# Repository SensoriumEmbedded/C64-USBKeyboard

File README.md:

# C64-USBKeyboard

## USB keyboard interface for Commodore 64

**Original code and C64 Key Pos Mapping:**
* C64keyboard - Commodore Keyboard library
* Copyright (c) 2022 Hartland PC LLC, Written by Robert VanHazinga

**Rewritten/updated for Teensy 3.6/4.1:**
* Copyright (c) 2023 Sensorium Embedded, Written by Travis Smith
* Raw keypresss detection for improved emulation
* Ability to Shift special macro keys to c64 (F2/4/6/8, Cursor up/left, etc) 
* Diagnostics loopback emulation
* Symbol mapping for readability and easy editing
* Improved code clarity, fixed bugs
* PCB designed/added

PCB assembly instructions can be found **[here.](PCB/PCB_Assembly.md)**

Questions?  Send e-mail to [Travis @ Sensorium](mailto:travis@sensoriumembedded.com)

Stand-alone and in-system pictures below.  Note that I have sockets above and below the Teensy module in my build. Actual build per BOM using headers will make it sit much lower (similar to the MT8808 chip)
||| 
|:--:|:--:|

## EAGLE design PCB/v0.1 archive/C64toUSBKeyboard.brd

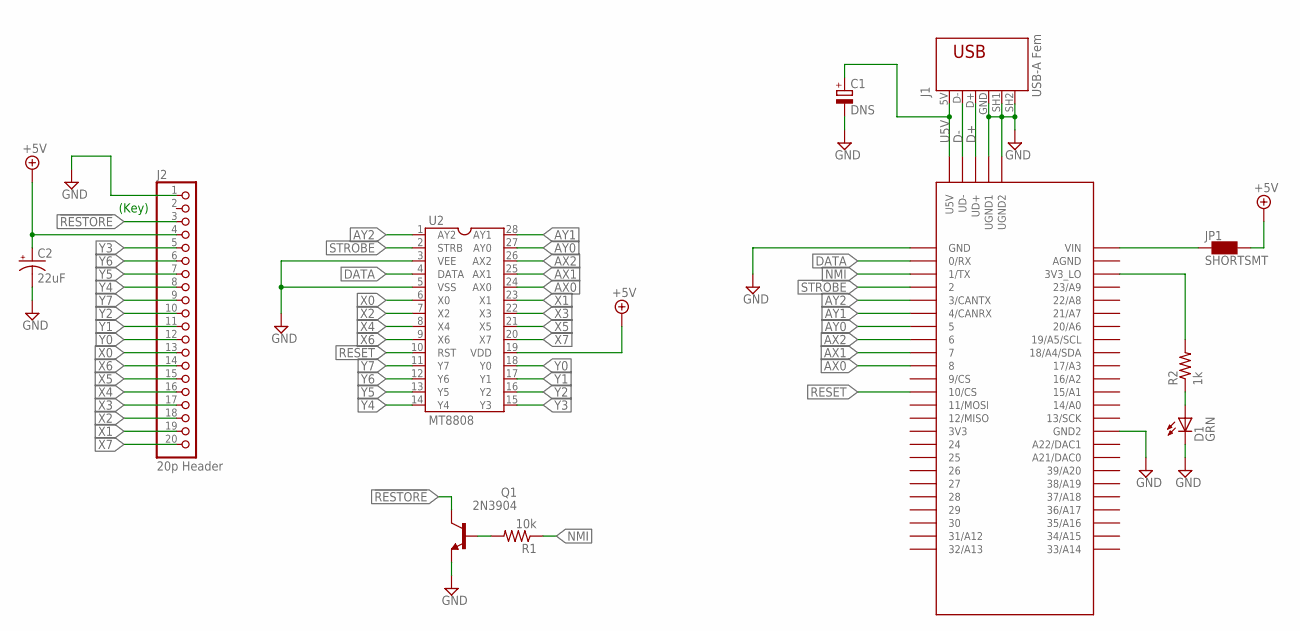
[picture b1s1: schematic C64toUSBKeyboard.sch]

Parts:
C1: DNS; A/3216-18W
C2: 22uF; E2,5-6
D1: GRN; LED-3MM-PTH
J1: USB-A Fem; USB
J2: 20p Header; 1X20_ROUND
JP1: SHORTSMT; SHORT
Q1: 2N3904; TO92
R1: 10k; 0207/10
R2: 1k; 0207/10
U1: TEENSY_3.6_4.1; TEENSY_3.5/3.6
U2: MT8808; DIL28-6

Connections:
3V3: R2.2, U1.3V3_LO
5V_TEENSY: JP1.1, U1.VIN
!RESTORE: J2.3, Q1.1 (C)
+5V: C2.+, J2.4, JP1.2, U2.19 (VDD)
AX0: U1.8, U2.24 (AX0)
AX1: U1.7, U2.25 (AX1)
AX2: U1.6, U2.26 (AX2)
AY0: U1.5, U2.27 (AY0)
AY1: U1.4/CANRX, U2.28 (AY1)
AY2: U1.3/CANTX, U2.1 (AY2)
D+: J1.D+ (3), U1.UD+
D-: J1.D- (2), U1.UD-
DATA: U1.0/RX, U2.4 (DATA)
GND: C1.-, C2.-, D1.K (C), J1.GND (4), J1.SH1 (5), J1.SH2 (6), J2.1, Q1.3 (E), U1.GND, U1.GND2, U1.UGND1, U1.UGND2, U2.3 (VEE), U2.5 (VSS)
LED_R: D1.A, R2.1
NMI: R1.1, U1.1/TX
NMI_R: Q1.2 (B), R1.2
RESET: U1.10/CS, U2.10 (RST)
STROBE: U1.2, U2.2 (STRB)
U5V: C1.+, J1.5V (1), U1.U5V
X0: J2.13, U2.6 (X0)
X1: J2.19, U2.23 (X1)
X2: J2.18, U2.7 (X2)
X3: J2.17, U2.22 (X3)
X4: J2.16, U2.8 (X4)
X5: J2.15, U2.21 (X5)
X6: J2.14, U2.9 (X6)
X7: J2.20, U2.20 (X7)
Y0: J2.12, U2.18 (Y0)
Y1: J2.11, U2.17 (Y1)
Y2: J2.10, U2.16 (Y2)
Y3: J2.5, U2.15 (Y3)
Y4: J2.8, U2.14 (Y4)
Y5: J2.7, U2.13 (Y5)
Y6: J2.6, U2.12 (Y6)
Y7: J2.9, U2.11 (Y7)

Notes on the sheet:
(Key)

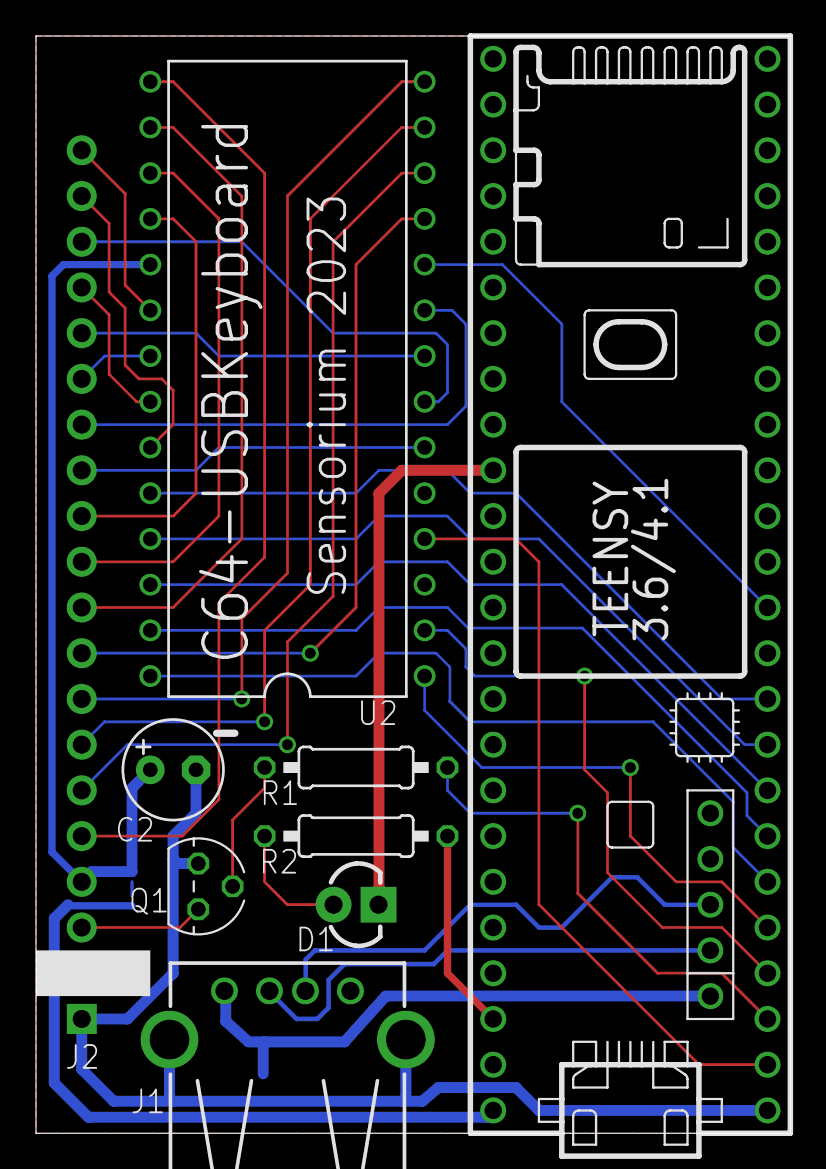
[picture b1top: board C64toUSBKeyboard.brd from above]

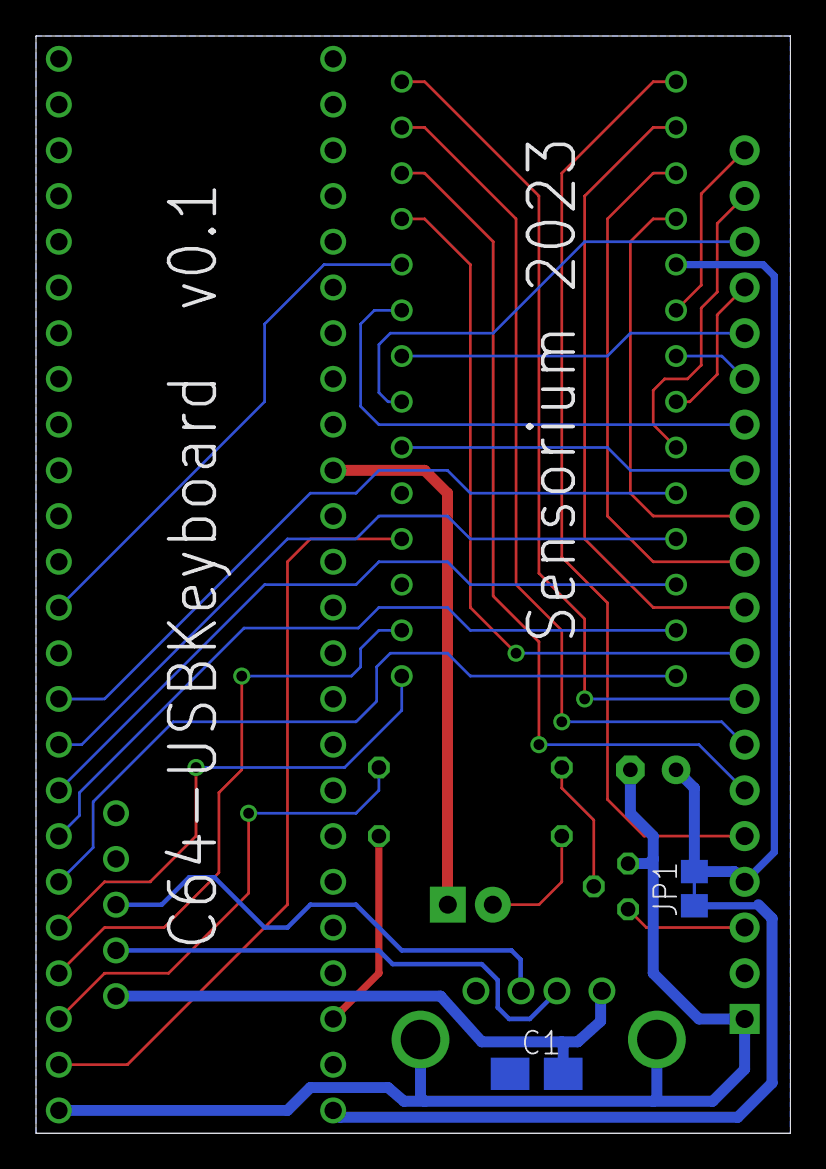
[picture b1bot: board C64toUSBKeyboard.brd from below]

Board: 2 copper layers, 41.9 x 61.0 mm, 11 parts (2 on the bottom side), 36 nets.

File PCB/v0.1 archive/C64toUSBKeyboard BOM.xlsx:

Qty | Value | Device | Package | Parts | Description | DIGIKEY | MANUF1 | MPN1 | VALUE
1 | 10k | R-US_0207/10 | 0207/10 | R1 | RESISTOR, American symbol
1 | 1k | R-US_0207/10 | 0207/10 | R2 | RESISTOR, American symbol
1 | 20p Header | HEADER-1X20ROUND | 1X20_ROUND | J2
1 | 22uF | CPOL-USE2.5-6 | E2,5-6 | C2 | POLARIZED CAPACITOR, American symbol
1 | 2N3904 | 2N3904 | TO92 | Q1 | NPN TRANSISTOR
1 | DNS | CPOL-EUA/3216-18W | A/3216-18W | C1 | POLARIZED CAPACITOR, European symbol
1 | GRN | LED-3MM-GRN | LED-3MM-PTH | D1 | LED 3.1MM PTH | 516-1293-ND | Broadcom Limited | HLMP-1503 | GRN
1 | MT8808 | DIL28 | DIL28-6 | U2 | Dual In Line
1 | SHORTSMT | SHORTSMT | SHORT | JP1
1 | TEENSY_3.6_4.1 | TEENSY_3.5/3.6 | TEENSY_3.5/3.6 | U1
1 | USB-A Fem | USB-787616 | USB | J1 | AMP connector

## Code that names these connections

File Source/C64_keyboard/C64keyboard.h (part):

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
//Teensy Pin Mapping
#define MT8808_DATA_PIN        0 // Sets selected cross switch on/off
#define NMI_RESTORE_PIN        1 // NMI (RESTORE KEY) PIN
#define MT8808_STROBE_PIN      2 // Strobe timing pulse (active high)
#define MT8808_RESET_PIN      10 // Reset all MT8808 cross switches to off (active high)
#define INDICATOR_LED_PIN     13 // LED on the Teensy
#define EXT_PULSE_OUT_PIN     32 // External Open Collector pulse low to simulate TeensyROM menu button push
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#define F10_PULSE_OUTPUT      0x43 // Dec 67: F10 pulses output pin EXT_PULSE_OUT_PIN low (TeensyROM Reset)
#define F11_LOOPBACK_KEY      0x44 // Dec 68: F11 sets diag loopback emulation
#define F12_MT8808_RESET_KEY  0x45 // Dec 69: F12 resets MT8808 
#define TAB_RESTORE_KEY       0x2B // Dec 43: Tab acts as Restore key
#define CAPSLOCK_TOG_KEY      0x39 // Dec 57: CapsLock key function toggle

//regular keys to C64 key map:
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
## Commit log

2023-04-02 v0.1 PCB design in Eagle PCB
2023-04-02 Initial code base
2023-04-05 Variable name clarification, cleanup
2023-04-06 Rewritten for Raw Key Press Improved clarity license/author info update timing/initialization fixes keymap additions via +SHIFT option
2023-04-06 ALT keys ignored, Esc becomes RUN/STOP
2023-04-09 Readme update
2023-04-09 Diag loopback mode added (F11)
2023-10-17 Gerbers PCB files and BOM details added
2023-10-17 added pictures, updated readme
2024-01-09 Comments added to describe xy bit location mapping
2024-01-09 Added Teensy connection headers to BOM, notes clarification
2024-01-09 PCB assy instructions, Top Render picture
2024-01-09 Format improvement
2024-01-18 New feature: F10 Pulses teensy pin 32 low, use for TeensyROM button Added USBHIDParser(s) for compatibility with latest library Added USBHub (in case used) Slowed down Teensy 4.1 (only) to 180MHz clo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
2024-07-31 50/60Hz out of pin 25 for TOD clock injection. toggle freq with F9

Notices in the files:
Source/C64_keyboard/C64keyboard.h:
This program is free software: you can redistribute it and/or modify
it under the terms of the GNU General Public License as published by
the Free Software Foundation, either version 3 of the License, or
(at your option) any later version.
